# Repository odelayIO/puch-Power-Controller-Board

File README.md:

# puch-Power-Controller-Board

## Overview

KiCAD 9.0 board design for the puch Power Controller Board.  This boad has the following features:

- Create a custom PCB to remotely control the power input for KR260, PYNQ-Z1, and both Pluto SDRs
- Single 12VDC power supply will source power to all 4 devices
- Add clean external power to both Pluto SDRs (minimum ripple noise)
- Add PWM fan controlled by the ESP32 micro-controller to adjust fan speed
- Integration to Home Assistant via MQTT device
- Utilize already existing parts in my stock :)

### High-Level Block Diagram

### KiCAD Images

## KiCAD Design

The design was created using KiCAD 9.0.  The following provides a brief description of the files in the repository and the BOM.

| Document                                           | Description                                                  |
| -------------------------------------------------- | ------------------------------------------------------------ |
| puch-Power-Controller-Board_Gerber-Output.zip      | The Gerber files for fabrication of the PCB board.  This board was fabricated at [OSH Park](https://oshpark.com/). |
| puch-power-controller-SCH.pdf                      | PDF copy of the schematic                                    |
| *.kicad_pcb, *.kicad_prl, *.kicad_sch, *.kicad_pro | The KiCAD 9.0 design files                                   |
| /lib/odelay and /lib/xiao                          | KiCAD 9.0 Library for the components                         |

### Bill Of Materials

| Reference           | Qty  | Value                         | Mouser Part #        |
| ------------------- | ---- | ----------------------------- | -------------------- |
| C1,C5,C9            | 3    | 0.33uF                        | 963-EMK212B7334KG-T  |
| C2,C6,C10           | 3    | 22uF                          | 581-TAJA226K006R     |
| C3,C7,C11           | 3    | 0.1uF                         | 963-LMK212SD104KG-T  |
| C4,C8,C12           | 3    | 47uF                          | 581-TAJA476K006SNJV  |
| FB1,FB2,FB3         | 3    | FerriteBead                   | 81-BLM21SP181SN1D    |
| H1,H2,H3,H4         | 4    | MountingHole                  |                      |
| J1,J3,J4,J6,J14,J17 | 6    | Conn_01x02_Pin                |                      |
| J2,J7               | 2    | USB_A                         | 538-67643-0910       |
| J5,J12              | 2    | Conn_01x04_Pin                | 538-22-05-3041       |
| J10,J13,J16         | 3    | Barrel_Jack_Switch            | 640-DCJ250-10-A-K1-K |
| Q1,Q2,Q3,Q4,Q5      | 5    | PMBT2222A                     | 750-MMBT2222A-HF     |
| R1,R2,R3,R4,R5      | 5    | 1K                            |                      |
| R9                  | 1    | 0ohm                          |                      |
| U1,U2,U3            | 3    | LM7805_TO220                  | 595-LM7805SX/NOPB    |
| U4                  | 1    | LM2596_Module                 |                      |
| U5                  | 1    | MOUDLE-SEEEDUINO-XIAO-ESP32C3 |                      |
| U6                  | 1    | 4-Channel-Relay-Module        |                      |

## Assembly

Re-flowed the LM7805 voltage regulators to PCB due to the large copper heat sink.

## Verification

PWM verification using oscilloscope

## XIAO ESP32-C3 Firmware

The firmware is in the Home Assistant Devices repository: 

https://github.com/odelayIO/Home-Assistant-Devices/tree/main/HA_MQTT_puch_rack_controller

### Home Assistant Integration:

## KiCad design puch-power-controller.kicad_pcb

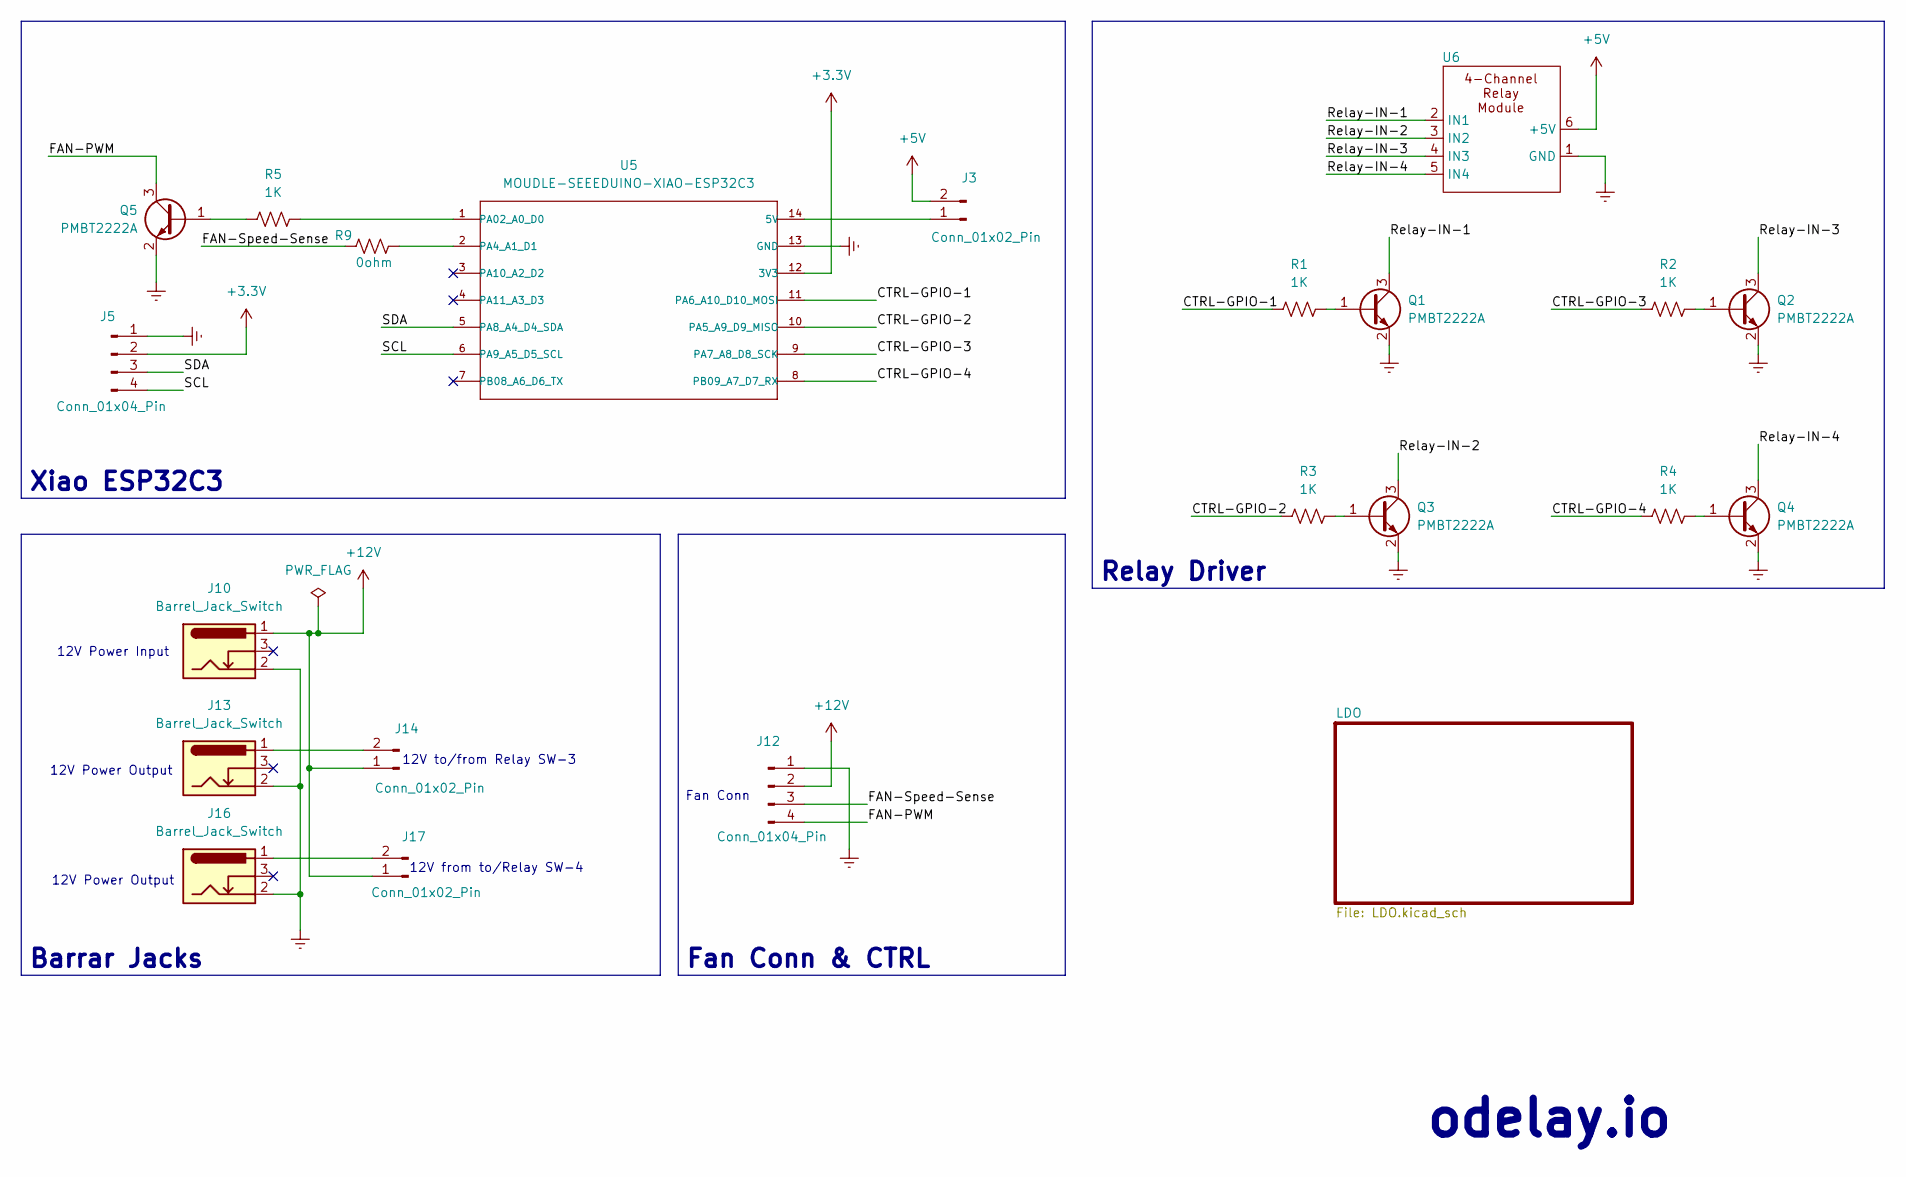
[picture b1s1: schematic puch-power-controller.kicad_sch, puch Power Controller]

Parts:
J3, J14, J17: Conn_01x02_Pin; PinHeader_1x02_P2.54mm_Vertical
J5, J12: Conn_01x04_Pin; PinHeader_1x04_P2.54mm_Vertical; Mouser Part # 538-22-05-3041
J10, J13, J16: Barrel_Jack_Switch; BarrelJack_GCT_DCJ200-10-A_Horizontal; Mouser Part # 640-DCJ250-10-A-K1-K
Q1, Q2, Q3, Q4, Q5: PMBT2222A; SOT-23; Mouser Part # 750-MMBT2222A-HF
R1, R2, R3, R4, R5: 1K; R_0805_2012Metric
R9: 0ohm; R_0805_2012Metric
U5: MOUDLE-SEEEDUINO-XIAO-ESP32C3; MOUDLE14P-SMD-2.54-21X17.8MM
U6: 4-Channel-Relay-Module; 4-Channel-Relay

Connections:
+3.3V: J5.2, U5.12 (3V3)
+5V: J3.2, U6.6 (+5V); also elsewhere on the board
+12V: J10.1, J12.2, J14.1, J17.1; also elsewhere on the board
/CTRL-GPIO-1: R1.1, U5.11 (PA6_A10_D10_MOSI)
/CTRL-GPIO-2: R3.1, U5.10 (PA5_A9_D9_MISO)
/CTRL-GPIO-3: R2.1, U5.9 (PA7_A8_D8_SCK)
/CTRL-GPIO-4: R4.1, U5.8 (PB09_A7_D7_RX)
/FAN-PWM: J12.4, Q5.3 (C)
/FAN-Speed-Sense: J12.3, R9.1
/Relay-IN-1: Q1.3 (C), U6.2 (IN1)
/Relay-IN-2: Q3.3 (C), U6.3 (IN2)
/Relay-IN-3: Q2.3 (C), U6.4 (IN3)
/Relay-IN-4: Q4.3 (C), U6.5 (IN4)
/SCL: J5.4, U5.6 (PA9_A5_D5_SCL)
/SDA: J5.3, U5.5 (PA8_A4_D4_SDA)
GNDREF: J5.1, J10.2, J12.1, J13.2, J16.2, Q1.2 (E), Q2.2 (E), Q3.2 (E), Q4.2 (E), Q5.2 (E), U5.13 (GND), U6.1 (GND); also elsewhere on the board
unnamed: J3.1, U5.14 (5V)
unnamed: J13.1, J14.2
unnamed: J16.1, J17.2
unnamed: Q1.1 (B), R1.2
unnamed: Q2.1 (B), R2.2
unnamed: Q3.1 (B), R3.2
unnamed: Q4.1 (B), R4.2
unnamed: Q5.1 (B), R5.1
unnamed: R5.2, U5.1 (PA02_A0_D0)
unnamed: R9.2, U5.2 (PA4_A1_D1)

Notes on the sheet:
12V Power Input
12V from to/Relay SW-4
odelay.io
12V Power Output
12V to/from Relay SW-3
Fan Conn
Xiao ESP32C3
Barrar Jacks
Relay Driver
Fan Conn & CTRL

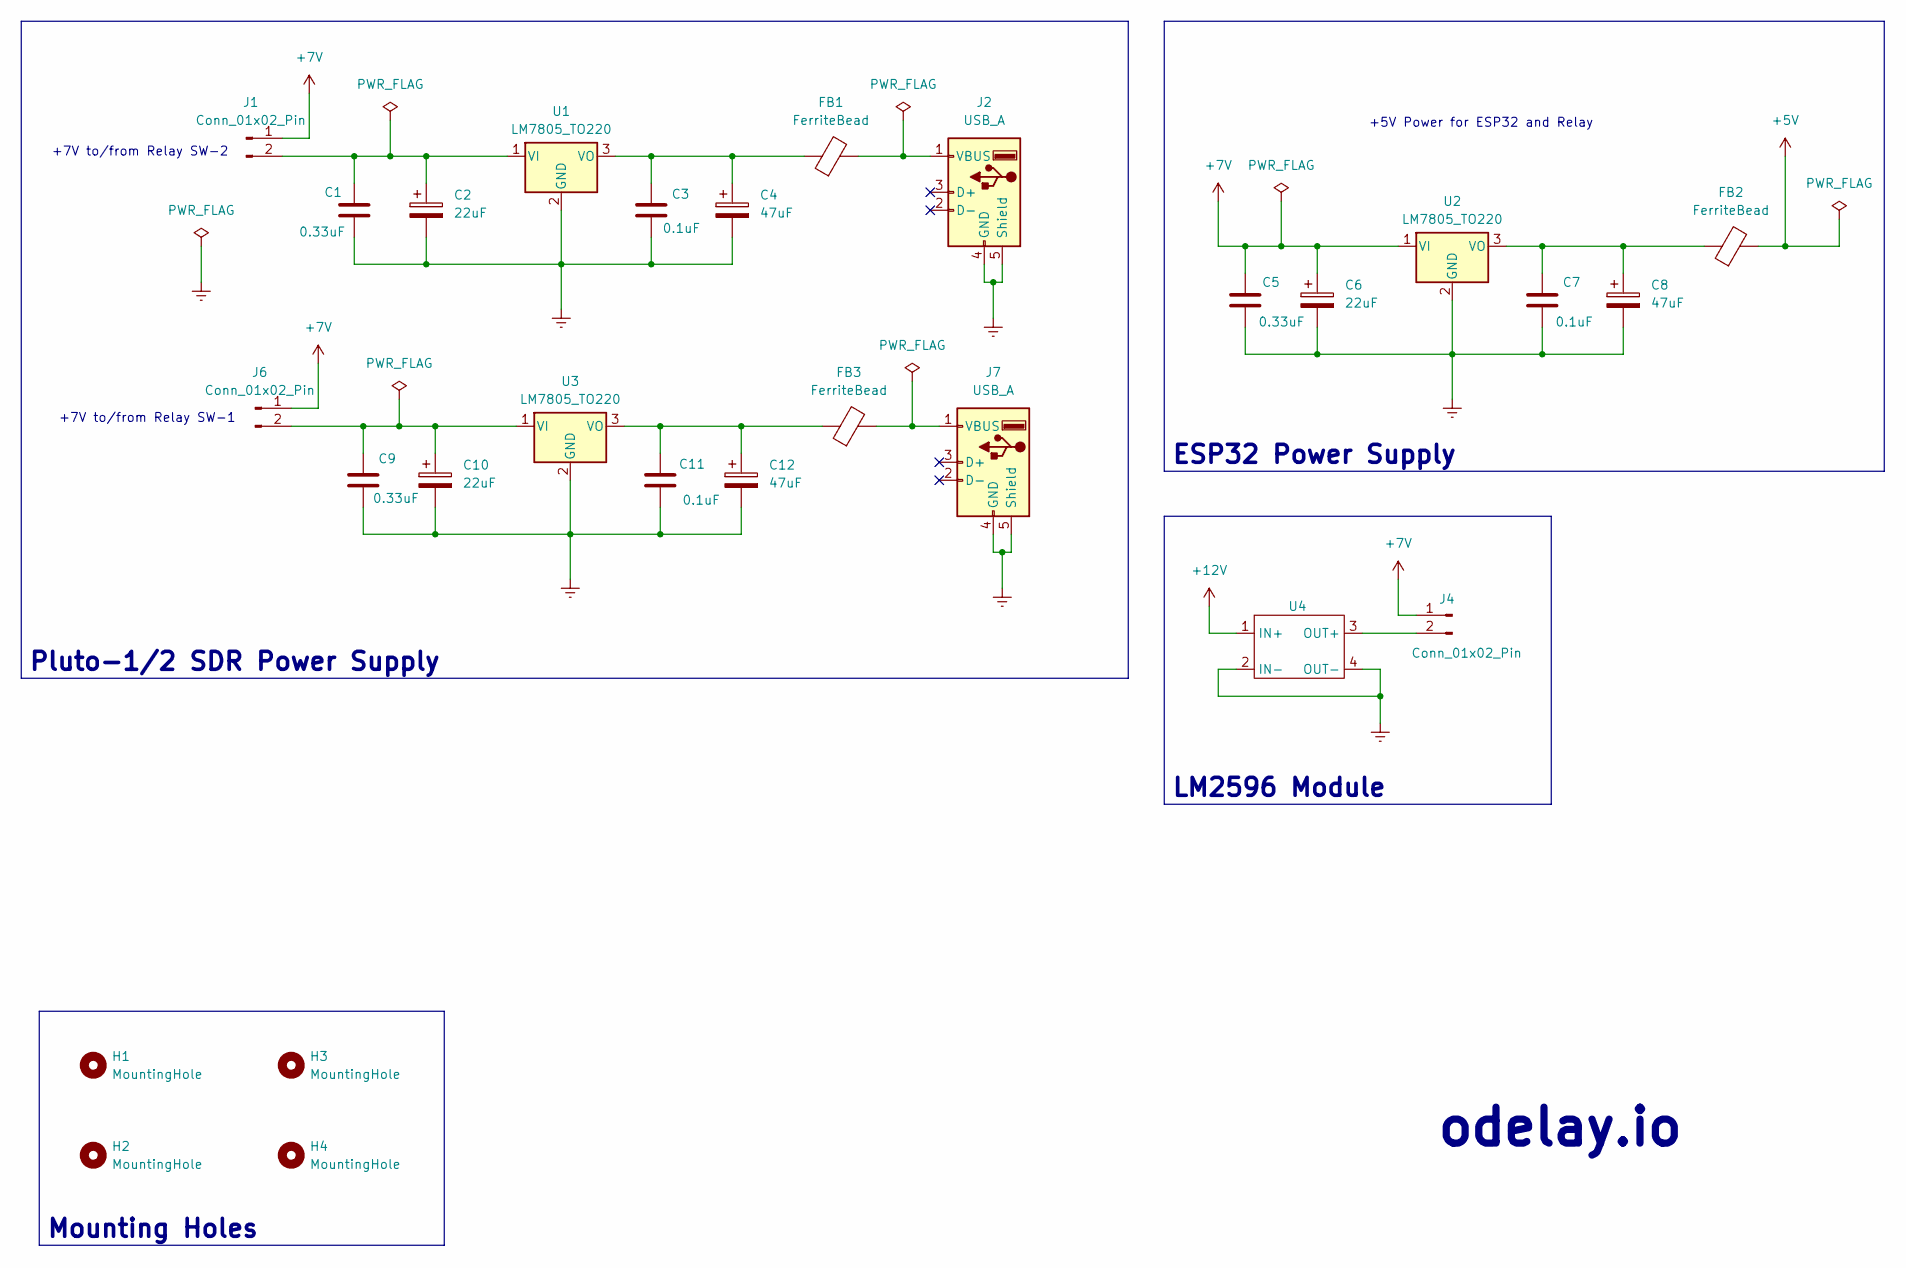
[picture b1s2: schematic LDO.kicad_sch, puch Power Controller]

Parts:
C1, C5, C9: 0.33uF; C_0805_2012Metric; Mouser Part # 963-EMK212B7334KG-T
C2, C6, C10: 22uF; C_1206_3216Metric; Mouser Part # 581-TAJA226K006R
C3, C7, C11: 0.1uF; C_0805_2012Metric; Mouser Part # 963-LMK212SD104KG-T
C4, C8, C12: 47uF; C_1206_3216Metric; Mouser Part # 581-TAJA476K006SNJV
FB1, FB2, FB3: FerriteBead; L_0805_2012Metric; Mouser Part # 81-BLM21SP181SN1D
H1, H2, H3, H4: MountingHole; MountingHole_2.7mm_M2.5
J1, J4, J6: Conn_01x02_Pin; PinHeader_1x02_P2.54mm_Vertical
J2, J7: USB_A; USB_A_Molex_67643_Horizontal; Mouser Part # 538-67643-0910
U1, U2, U3: LM7805_TO220; TO-263-3_TabPin2; Mouser Part # 595-LM7805SX/NOPB
U4: LM2596_Module

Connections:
+5V: FB2.2; also elsewhere on the board
+7V: C5.1, C6.1, J1.1, J4.1, J6.1, U2.1 (VI)
+12V: U4.1 (IN+); also elsewhere on the board
GNDREF: C1.2, C2.2, C3.2, C4.2, C5.2, C6.2, C7.2, C8.2, C9.2, C10.2, C11.2, C12.2, J2.4 (GND), J2.5 (Shield), J7.4 (GND), J7.5 (Shield), U1.2 (GND), U2.2 (GND), U3.2 (GND), U4.2 (IN-), U4.4 (OUT-); also elsewhere on the board
unnamed: C1.1, C2.1, J1.2, U1.1 (VI)
unnamed: FB1.2, J2.1 (VBUS)
unnamed: J4.2, U4.3 (OUT+)
unnamed: C9.1, C10.1, J6.2, U3.1 (VI)
unnamed: FB3.2, J7.1 (VBUS)
unnamed: C3.1, C4.1, FB1.1, U1.3 (VO)
unnamed: C7.1, C8.1, FB2.1, U2.3 (VO)
unnamed: C11.1, C12.1, FB3.1, U3.3 (VO)

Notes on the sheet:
+7V to/from Relay SW-1
+5V Power for ESP32 and Relay
odelay.io
+7V to/from Relay SW-2
LM2596 Module
ESP32 Power Supply
Pluto-1/2 SDR Power Supply
Mounting Holes

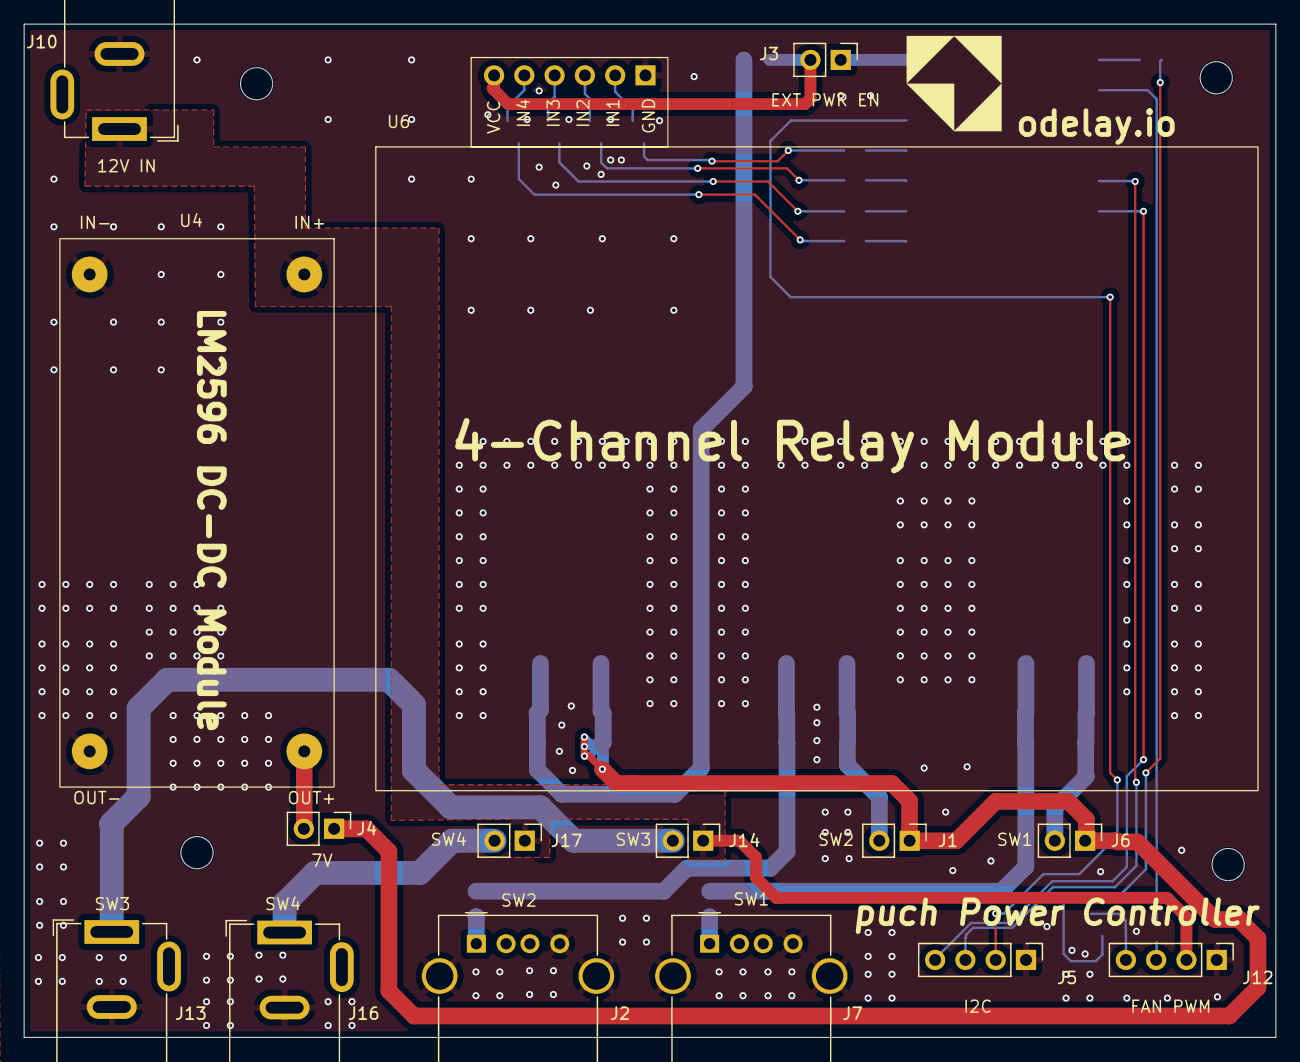
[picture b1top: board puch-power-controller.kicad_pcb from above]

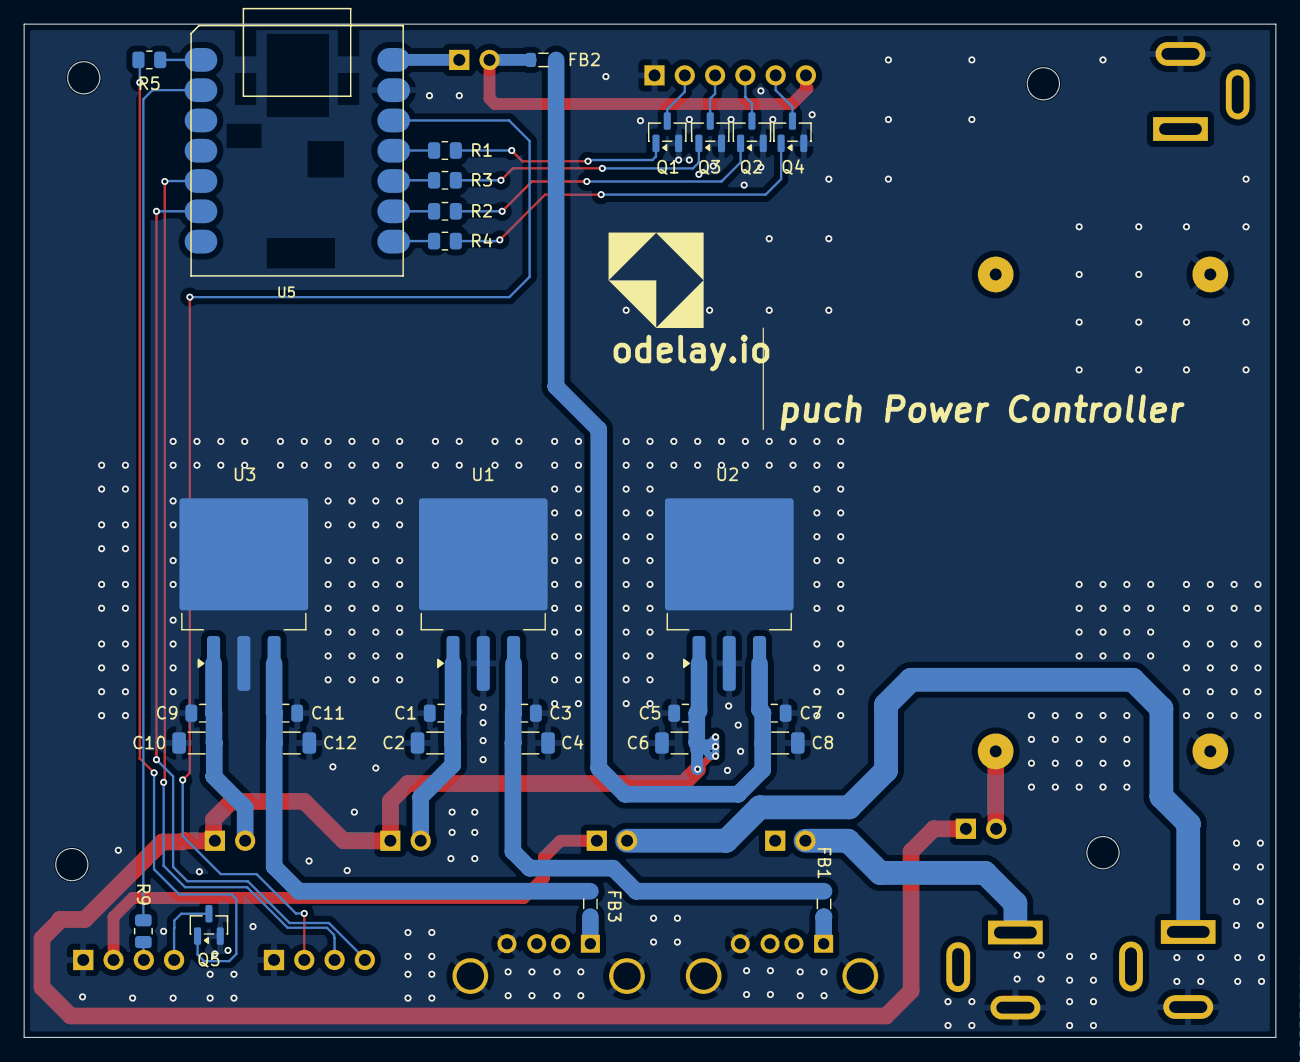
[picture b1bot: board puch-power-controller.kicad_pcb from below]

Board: 2 copper layers, 105.0 x 85.0 mm, 49 parts (30 on the bottom side), 35 nets.

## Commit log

2026-01-25 adding design files
2026-01-31 added 3D model for XIAO
2026-02-13 updated documentation
2026-02-13 added HA GUI
